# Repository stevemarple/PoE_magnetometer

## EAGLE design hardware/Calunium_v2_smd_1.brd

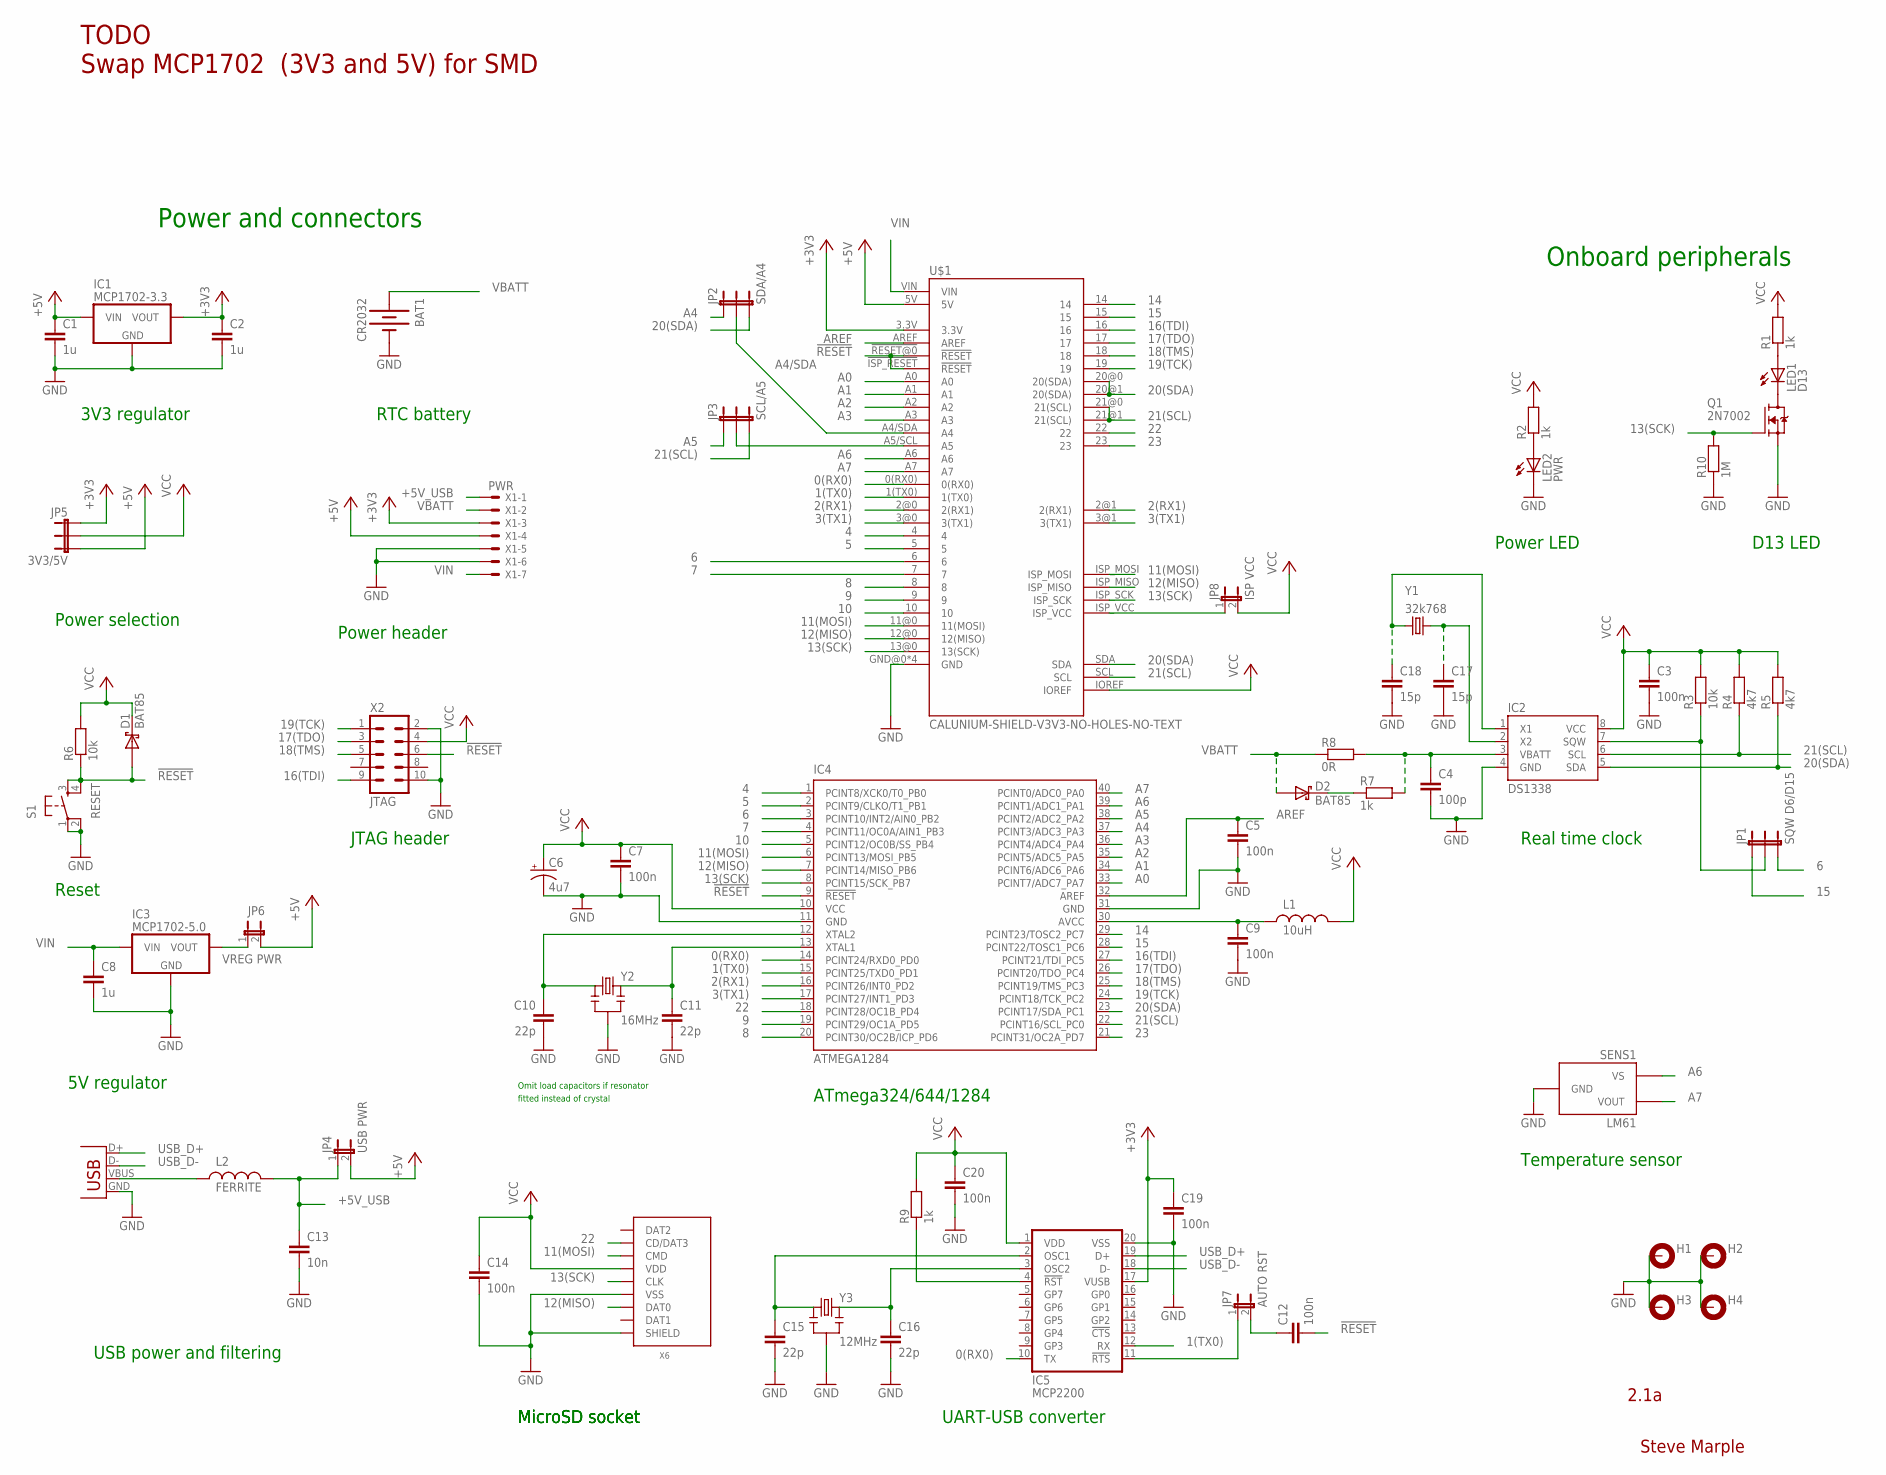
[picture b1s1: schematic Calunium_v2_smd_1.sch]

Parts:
BAT1: CR2032; BATTCOM_20MM_PTH
C1, C2, C8: 1u; 1206-HAND
C3, C5, C7, C9, C12, C14, C19, C20: 100n; 1206-HAND
C4: 100p; 1206-HAND
C6: 4u7; CPOL-RADIAL-10UF-25V
C10, C11, C15, C16: 22p; 0805-HAND
C13: 10n; 1206-HAND
C17, C18: 15p; 0805-HAND
D1, D2: BAT85; SOT23-3-HAND
H1, H2, H3, H4: MOUNT-PAD-ROUND3.0; 3,0-PAD
IC1: MCP1702-3.3; TO-92
IC2: DS1338; SO08
IC3: MCP1702-5.0; TO-92
IC4: ATMEGA1284; DIL40
IC5: MCP2200; SO20
JP1: SQW D6/D15; 1X03
JP2: SDA/A4; 1X03
JP3: SCL/A5; 1X03
JP4: USB PWR; 1X02
JP5: 3V3/5V; 1X03
JP6: VREG PWR; 1X02
JP7: AUTO RST; 1X02
JP8: ISP VCC; 1X02
L1: 10uH; 1210-HAND
L2: FERRITE; 0805-HAND
LED1: D13; LED3MM
LED2: PWR; LED3MM
Q1: 2N7002; SOT23-3-ROTATED
R1, R2, R7, R9: 1k; 1206-HAND
R3, R6: 10k; 1206-HAND
R4, R5: 4k7; 1206-HAND
R8: 0R; 1206-HAND
R10: 1M; 1206-HAND
S1: RESET; TACTILE-PTH
SENS1: LM61; TO-92
U$1: CALUNIUM-SHIELD-V3V3-NO-HOLES-NO-TEXT; CALUNIUM-SHIELD-NO-OUTLINE-NO-HOLES-NO-TEXT-V3
X1: PWR; 22-23-2071
X2: JTAG; CON-HARTING-ML10
X3: USB; USB-B-PTH
X6: MICRO-SD-SOCKETHIROSE-DM3D; MICRO-SD-SOCKET-HIROSE-DM3D
Y1: 32k768; TC38H
Y2: 16MHz; HC49U-V-RESONATOR
Y3: 12MHz; HC49U-V-RESONATOR

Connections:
0(RX0): IC4.14 (PCINT24/RXD0_PD0), IC5.10 (TX), U$1.0(RX0)
1(TX0): IC4.15 (PCINT25/TXD0_PD1), IC5.12 (RX), U$1.1(TX0)
2(RX1): IC4.16 (PCINT26/INT0_PD2), U$1.2@0 (2(RX1)), U$1.2@1 (2(RX1))
3(TX1): IC4.17 (PCINT27/INT1_PD3), U$1.3@0 (3(TX1)), U$1.3@1 (3(TX1))
4: IC4.1 (PCINT8/XCK0/T0_PB0), U$1.4
5: IC4.2 (PCINT9/CLKO/T1_PB1), U$1.5
6: IC4.3 (PCINT10/INT2/AIN0_PB2), JP1.3, U$1.6
7: IC4.4 (PCINT11/OC0A/AIN1_PB3), U$1.7
8: IC4.20 (PCINT30/OC2B/ICP_PD6), U$1.8
9: IC4.19 (PCINT29/OC1A_PD5), U$1.9
10: IC4.5 (PCINT12/OC0B/SS_PB4), U$1.10
11(MOSI): IC4.6 (PCINT13/MOSI_PB5), U$1.11@0 (11(MOSI)), U$1.ISP_MOSI, X6.CMD
12(MISO): IC4.7 (PCINT14/MISO_PB6), U$1.12@0 (12(MISO)), U$1.ISP_MISO, X6.DAT0
13(SCK): IC4.8 (PCINT15/SCK_PB7), Q1.1 (G), R10.2, U$1.13@0 (13(SCK)), U$1.ISP_SCK, X6.CLK
14: IC4.29 (PCINT23/TOSC2_PC7), U$1.14
15: IC4.28 (PCINT22/TOSC1_PC6), JP1.1, U$1.15
16(TDI): IC4.27 (PCINT21/TDI_PC5), U$1.16, X2.9 (TDI)
17(TDO): IC4.26 (PCINT20/TDO_PC4), U$1.17, X2.3 (TDO)
18(TMS): IC4.25 (PCINT19/TMS_PC3), U$1.18, X2.5 (TMS)
19(TCK): IC4.24 (PCINT18/TCK_PC2), U$1.19, X2.1 (TCK)
20(SDA): IC2.5 (SDA), IC4.23 (PCINT17/SDA_PC1), JP2.3, R5.1, U$1.20@0 (20(SDA)), U$1.20@1 (20(SDA)), U$1.SDA
21(SCL): IC2.6 (SCL), IC4.22 (PCINT16/SCL_PC0), JP3.3, R4.1, U$1.21@0 (21(SCL)), U$1.21@1 (21(SCL)), U$1.SCL
22: IC4.18 (PCINT28/OC1B_PD4), U$1.22, X6.CD/DAT3
23: IC4.21 (PCINT31/OC2A_PD7), U$1.23
!MCP2200_RESET: IC5.4 (!RST), R9.1
!RESET: C12.2, D1.1 (A), IC4.9 (!RESET), R6.1, S1.3, S1.4, U$1.!ISP_RESET (!RESET), U$1.!RESET@0 (!RESET), X2.6 (!SRST)
+3V3: C2.1, C19.1, IC1.3 (VOUT), IC5.17 (VUSB), JP5.1, U$1.3.3V, X1.3
+5V: C1.1, IC1.2 (VIN), JP4.2, JP5.3, JP6.2, U$1.5V, X1.4
+5V_USB: C13.1, JP4.1, L2.2, X1.1
A0: IC4.33 (PCINT7/ADC7_PA7), U$1.A0
A1: IC4.34 (PCINT6/ADC6_PA6), U$1.A1
A2: IC4.35 (PCINT5/ADC5_PA5), U$1.A2
A3: IC4.36 (PCINT4/ADC4_PA4), U$1.A3
A4: IC4.37 (PCINT3/ADC3_PA3), JP2.1
A4/SDA: JP2.2, U$1.A4/SDA (A4)
A5: IC4.38 (PCINT2/ADC2_PA2), JP3.1
A5/SCL: JP3.2, U$1.A5/SCL (A5)
A6: IC4.39 (PCINT1/ADC1_PA1), SENS1.1 (VS), U$1.A6
A7: IC4.40 (PCINT0/ADC0_PA0), SENS1.2 (VOUT), U$1.A7
AREF: C5.1, IC4.32 (AREF), U$1.AREF
AUTO_RESET: IC5.11 (!RTS), JP7.1
AVCC: C9.1, IC4.30 (AVCC), L1.1
GND: BAT1.2 (-), C1.2, C2.2, C3.2, C4.2, C5.2, C6.2 (-), C7.2, C8.2, C9.2, C10.2, C11.2, C13.2, C14.2, C15.2, C16.2, C17.2, C18.2, C19.2, C20.2, H1.B3,0, H2.B3,0, H3.B3,0, H4.B3,0, IC1.1 (GND), IC2.4 (GND), IC3.1 (GND), IC4.11 (GND), IC4.31 (GND), IC5.20 (VSS), LED2.K (C), Q1.2 (S), R10.1, S1.1, S1.2, SENS1.3 (GND), U$1.GND@0 (GND), U$1.GND@1 (GND), U$1.GND@2 (GND), U$1.GND@3 (GND), X1.5, X1.6, X2.2 (GND), X2.10 (GND), X3.GND, X6.GND (VSS), X6.SHIELD@0 (SHIELD), Y2.GND (2), Y3.GND (2)
unnamed: C11.1, IC4.13 (XTAL1), Y2.2 (3)
unnamed: C10.1, IC4.12 (XTAL2), Y2.1
unnamed: LED1.A, R1.1
unnamed: LED1.K (C), Q1.3 (D)
unnamed: C18.1, IC2.1 (X1), Y1.2
unnamed: JP8.1, U$1.ISP_VCC
unnamed: C16.1, IC5.3 (OSC2), Y3.2 (3)
unnamed: LED2.A, R2.1
unnamed: D2.3 (C), R7.1
unnamed: C4.1, IC2.3 (VBATT), R7.2, R8.2
unnamed: C17.1, IC2.2 (X2), Y1.1
unnamed: IC3.3 (VOUT), JP6.1
unnamed: C12.1, JP7.2
unnamed: L2.1, X3.VBUS
unnamed: C15.1, IC5.2 (OSC1), Y3.1
SQW: IC2.7 (SQW), JP1.2, R3.1
USB_D+: IC5.19 (D+), X3.D+
USB_D-: IC5.18 (D-), X3.D-
VBATT: BAT1.1 (+), D2.1 (A), R8.1, X1.2
VCC: C3.1, C6.1 (+), C7.1, C14.1, C20.1, D1.3 (C), IC2.8 (VCC), IC4.10 (VCC), IC5.1 (VDD), JP5.2, JP8.2, L1.2, R1.2, R2.2, R3.2, R4.2, R5.2, R6.2, R9.2, U$1.IOREF, X2.4 (VTREF), X6.VDD
VIN: C8.1, IC3.2 (VIN), U$1.VIN, X1.7

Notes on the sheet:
Power and connectors
Onboard peripherals
Real time clock
Temperature sensor
ATmega324/644/1284
USB power and filtering
JTAG header
D13 LED
Reset
Power selection
Power header
3V3 regulator
RTC battery
Power LED
Steve Marple
2.1a
5V regulator
Omit load capacitors if resonator
fitted instead of crystal
MicroSD socket
UART-USB converter
TODO Swap MCP1702 (3V3 and 5V) for SMD

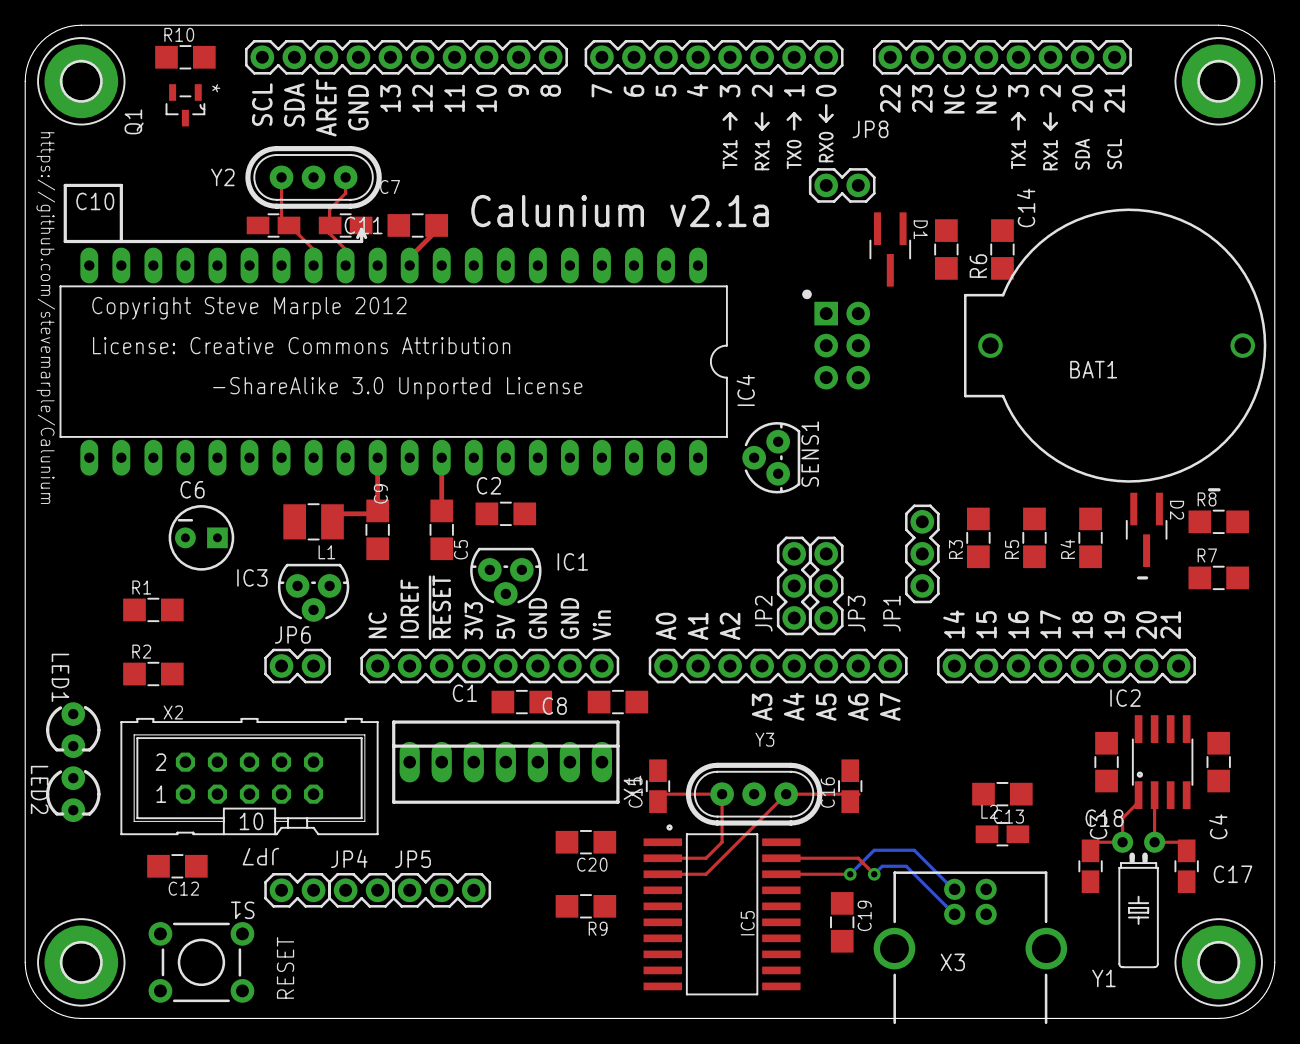
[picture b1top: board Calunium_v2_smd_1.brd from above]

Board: 2 copper layers, 99.1 x 78.7 mm, 65 parts (1 on the bottom side), 64 nets.

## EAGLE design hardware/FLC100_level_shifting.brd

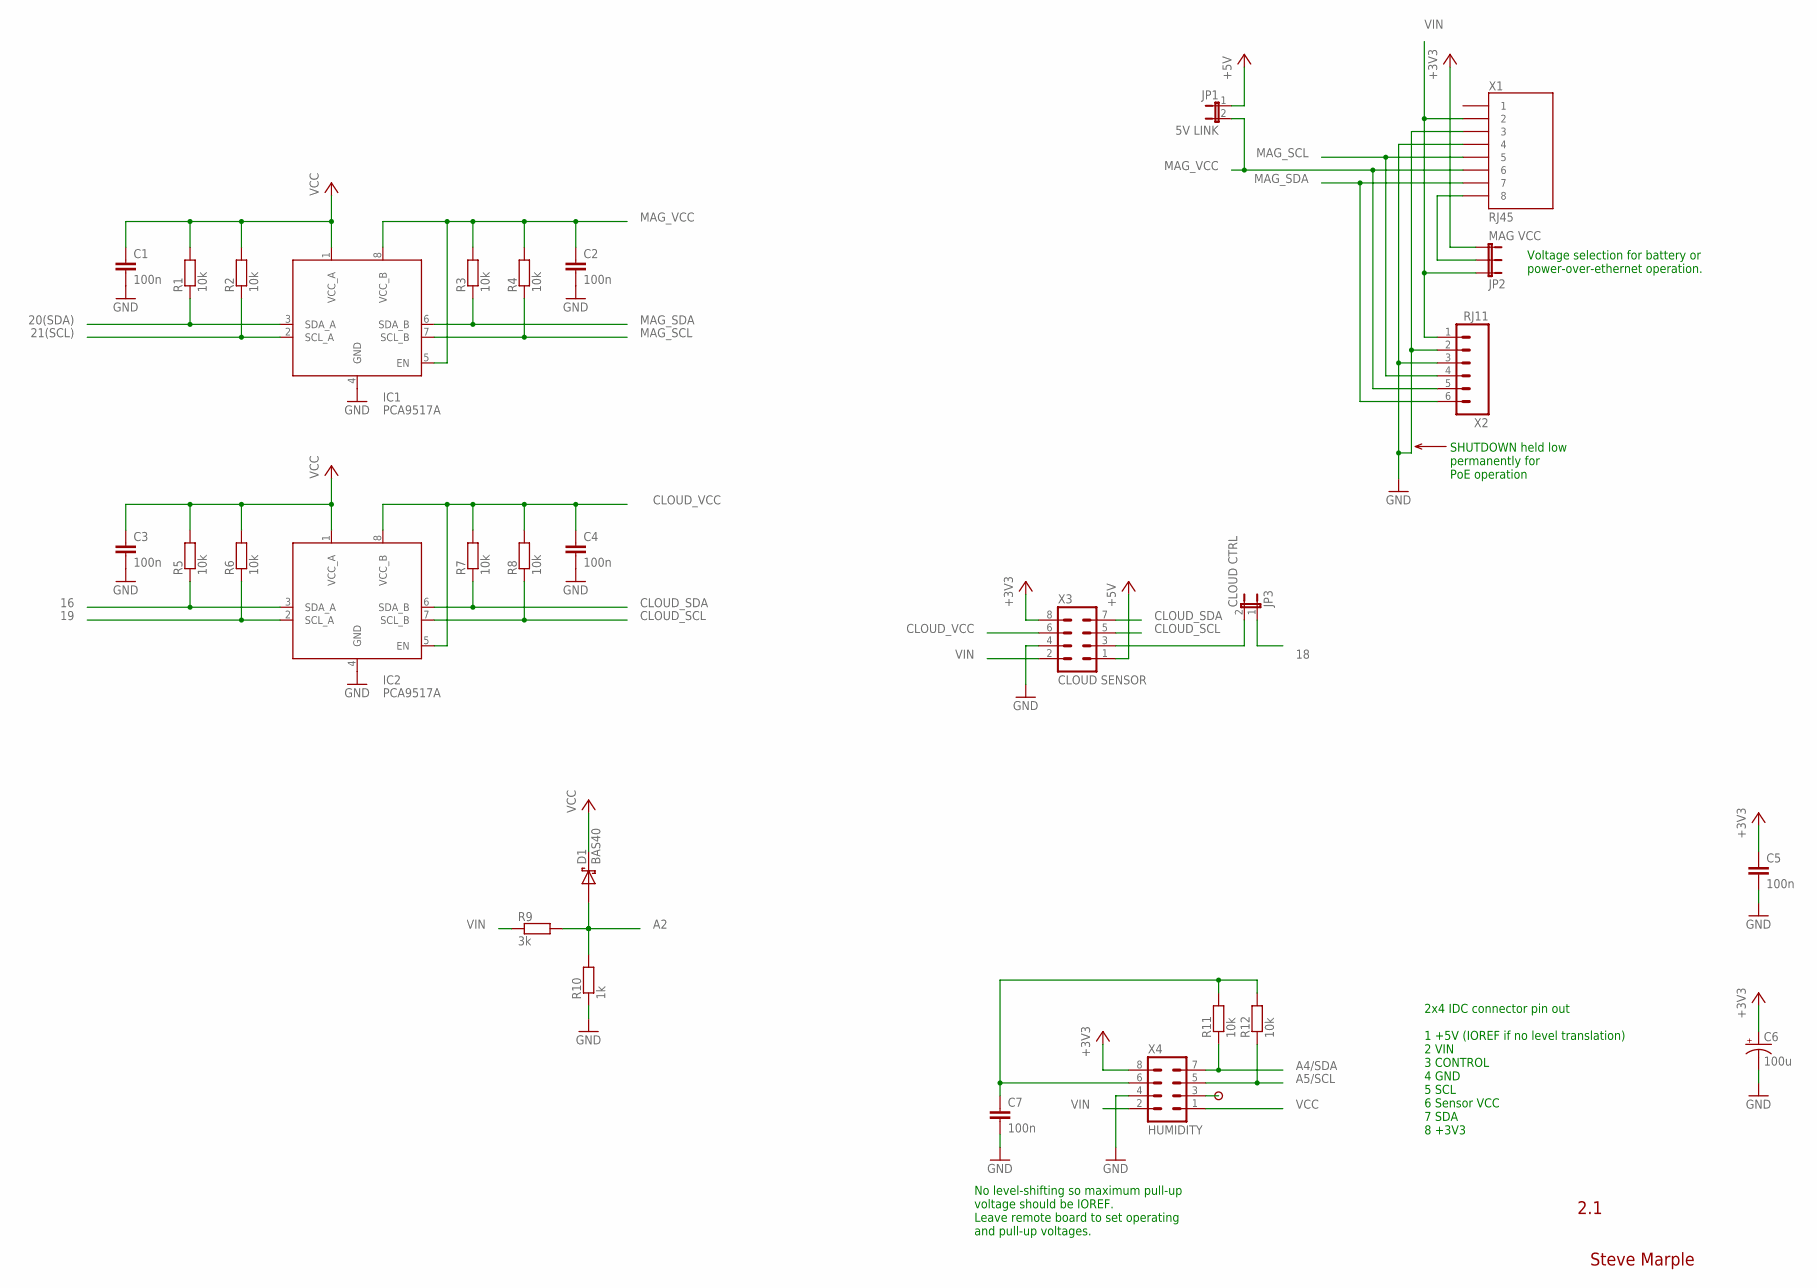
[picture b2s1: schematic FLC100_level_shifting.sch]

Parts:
C1, C2, C3, C4, C5, C7: 100n; 1206-HAND
C6: 100u; CPOL-RADIAL-10UF-25V
D1: BAS40; SOT23-3-HAND
IC1, IC2: PCA9517A; SO08
JP1: 5V LINK; 1X02
JP2: MAG VCC; 1X03
JP3: CLOUD CTRL; 1X02
R1, R2, R3, R4, R5, R6, R7, R8, R11, R12: 10k; 1206-HAND
R9: 3k; 1206-HAND
R10: 1k; 1206-HAND
U$5: PAD
X1: RJ45; RJ45-8
X2: RJ11; RJ11-6
X3: CLOUD SENSOR; ML8
X4: HUMIDITY; ML8

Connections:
16: IC2.3 (SDA_A), R5.1
18: JP3.1
19: IC2.2 (SCL_A), R6.1
20(SDA): IC1.3 (SDA_A), R1.1
21(SCL): IC1.2 (SCL_A), R2.1
+3V3: C5.1, C6.1 (+), JP2.3, X3.8, X4.8
+5V: JP1.1, X3.1
A2: D1.1 (A), R9.2, R10.2
A4/SDA: R11.1, X4.7
A5/SCL: R12.1, X4.5
CLOUD_SCL: IC2.7 (SCL_B), R8.1, X3.5
CLOUD_SDA: IC2.6 (SDA_B), R7.1, X3.7
CLOUD_VCC: C4.1, IC2.5 (EN), IC2.8 (VCC_B), R7.2, R8.2, X3.6
GND: C1.2, C2.2, C3.2, C4.2, C5.2, C6.2 (-), C7.2, IC1.4 (GND), IC2.4 (GND), R10.1, X1.3, X1.4, X2.2, X2.3, X3.4, X4.4
MAG_SCL: IC1.7 (SCL_B), R4.1, X1.5, X2.4
MAG_SDA: IC1.6 (SDA_B), R3.1, X1.7, X2.6
MAG_VCC: C2.1, IC1.5 (EN), IC1.8 (VCC_B), JP1.2, R3.2, R4.2, X1.6, X2.5
unnamed: JP3.2, X3.3
unnamed: JP2.2, X1.8
unnamed: U$5.1, X4.3
unnamed: C7.1, R11.2, R12.2, X4.6
VCC: C1.1, C3.1, D1.3 (C), IC1.1 (VCC_A), IC2.1 (VCC_A), R1.2, R2.2, R5.2, R6.2, X4.1
VIN: JP2.1, R9.1, X1.2, X2.1, X3.2, X4.2

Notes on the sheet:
2.1
Steve Marple
Voltage selection for battery or power-over-ethernet operation.
No level-shifting so maximum pull-up voltage should be IOREF. Leave remote board to set operating and pull-up voltages.
2x4 IDC connector pin out 1 +5V (IOREF if no level translation) 2 VIN 3 CONTROL 4 GND 5 SCL 6 Sensor VCC 7 SDA 8 +3V3
SHUTDOWN held low permanently for PoE operation

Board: 2 copper layers, 30 parts (0 on the bottom side), 22 nets, no tracks yet.

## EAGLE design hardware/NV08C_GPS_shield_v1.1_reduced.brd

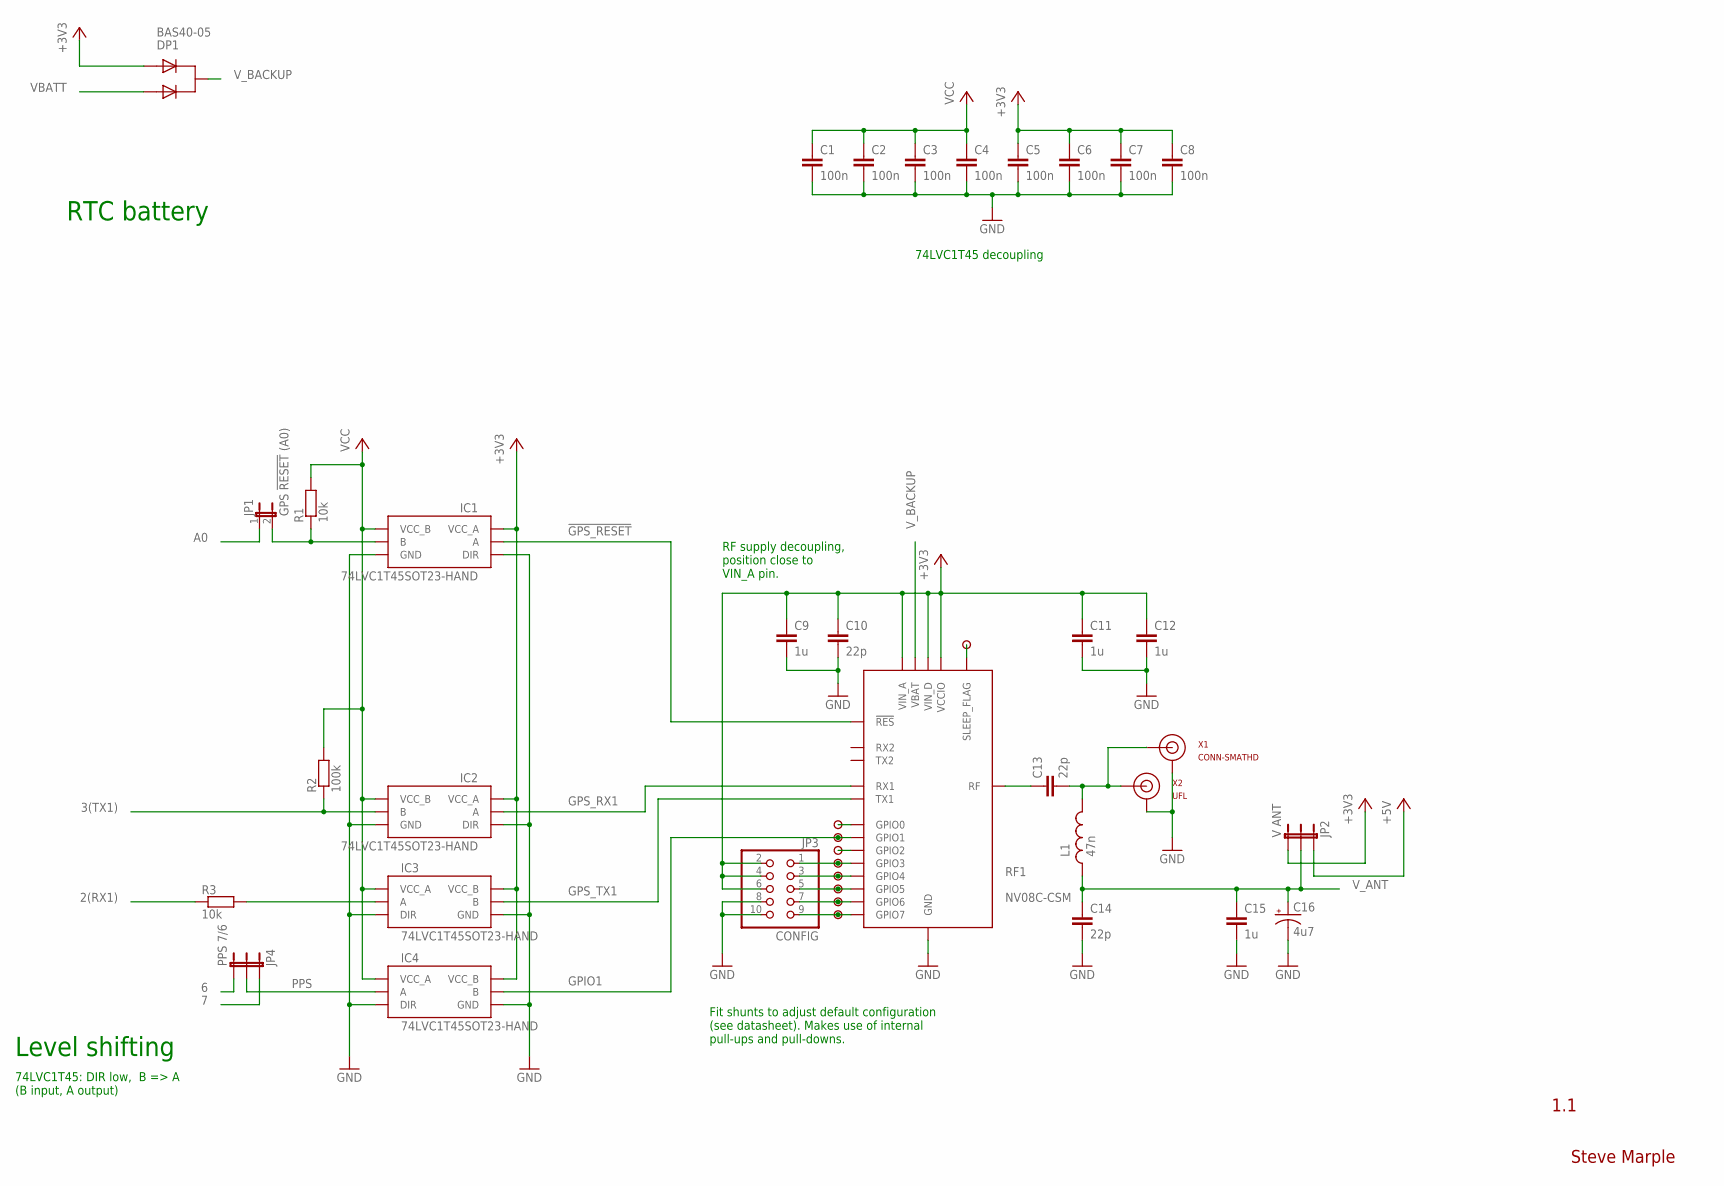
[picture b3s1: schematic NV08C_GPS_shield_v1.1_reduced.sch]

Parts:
C1, C2, C3, C4, C5, C6, C7, C8: 100n; 1206-HAND
C9, C11, C12, C15: 1u; 1206-HAND
C10, C13, C14: 22p; 0805-HAND
C16: 4u7; CPOL-RADIAL-10UF-25V
DP1: BAS40-05; SOT23-3-HAND
IC1, IC2, IC3, IC4: 74LVC1T45SOT23-HAND; SOT23-6-HAND
JP1: GPS !RESET! (A0); 1X02
JP2: V ANT; 1X03
JP3: CONFIG; 2X05
JP4: PPS 7/6; 1X03
L1: 47n; 0805-HAND
R1, R3: 10k; 1206-HAND
R2: 100k; 1206-HAND
RF1: NV08C-CSM; NVC08C-CSM-HAND
U$1, U$2, U$3, U$5, U$6, U$7, U$8, U$9: PAD
U$4: ?; PAD
X1: CONN-SMATHD; SMA-THD
X2: UFL; CONN-UFL-HAND-SOLDERING

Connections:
2(RX1): R3.1
3(TX1): IC2.4 (B), R2.1
6: JP4.3
7: JP4.1
!GPS_RESET: IC1.3 (A), RF1.P$25 (!RES)
+3V3: C5.1, C6.1, C7.1, C8.1, C9.1, C10.1, C11.1, C12.1, DP1.2 (A2), IC1.1 (VCC_A), IC2.1 (VCC_A), IC3.6 (VCC_B), IC4.6 (VCC_B), JP2.3, JP3.2, JP3.4, JP3.6, RF1.P$8 (VIN_A), RF1.P$26 (VIN_D), RF1.P$28 (VCCIO)
+5V: JP2.1
A0: JP1.1
GND: C1.2, C2.2, C3.2, C4.2, C5.2, C6.2, C7.2, C8.2, C9.2, C10.2, C11.2, C12.2, C14.2, C15.2, C16.2 (-), IC1.2 (GND), IC1.5 (DIR), IC2.2 (GND), IC2.5 (DIR), IC3.2 (GND), IC3.5 (DIR), IC4.2 (GND), IC4.5 (DIR), JP3.8, JP3.10, RF1.P$3 (GND), RF1.P$9 (GND), RF1.P$10 (GND), RF1.P$11 (GND), RF1.P$12 (GND), RF1.P$13 (GND), RF1.P$14 (GND), RF1.P$16 (GND), RF1.P$17 (GND), RF1.P$18 (GND), RF1.P$19 (GND), RF1.P$22 (GND), RF1.P$24 (GND), RF1.P$27 (GND), RF1.P$29 (GND), RF1.P$34 (GND), X1.GND@0 (GND), X1.GND@1 (GND), X1.GND@2 (GND), X1.GND@3 (GND), X2.GND@0 (GND), X2.GND@1 (GND)
GPIO0: RF1.P$20 (GPIO0), U$2.1
GPIO1: IC4.4 (B), RF1.P$2 (GPIO1), U$3.1
GPIO2: RF1.P$1 (GPIO2), U$4.1
GPIO3: JP3.1, RF1.P$6 (GPIO3), U$5.1
GPIO4: JP3.3, RF1.P$7 (GPIO4), U$6.1
GPIO5: JP3.5, RF1.P$4 (GPIO5), U$7.1
GPIO6: JP3.7, RF1.P$35 (GPIO6), U$8.1
GPIO7: JP3.9, RF1.P$5 (GPIO7), U$9.1
GPS_RX1: IC2.3 (A), RF1.P$33 (RX1)
GPS_TX1: IC3.4 (B), RF1.P$32 (TX1)
unnamed: C13.2, L1.2, X1.SIG (SIGNAL), X2.SIGNAL
unnamed: IC3.3 (A), R3.2
unnamed: C13.1, RF1.P$15 (RF)
unnamed: IC1.4 (B), JP1.2, R1.1
PPS: IC4.3 (A), JP4.2
SLEEP_FLAG: RF1.P$21 (SLEEP_FLAG), U$1.1
VBATT: DP1.1 (A1)
VCC: C1.1, C2.1, C3.1, C4.1, IC1.6 (VCC_B), IC2.6 (VCC_B), IC3.1 (VCC_A), IC4.1 (VCC_A), R1.2, R2.2
V_ANT: C14.1, C15.1, C16.1 (+), JP2.2, L1.1
V_BACKUP: DP1.3 (C), RF1.P$23 (VBAT)

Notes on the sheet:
1.1
Steve Marple
Level shifting
RTC battery
74LVC1T45: DIR low, B => A (B input, A output)
RF supply decoupling, position close to VIN_A pin.
Fit shunts to adjust default configuration (see datasheet). Makes use of internal pull-ups and pull-downs.
74LVC1T45 decoupling

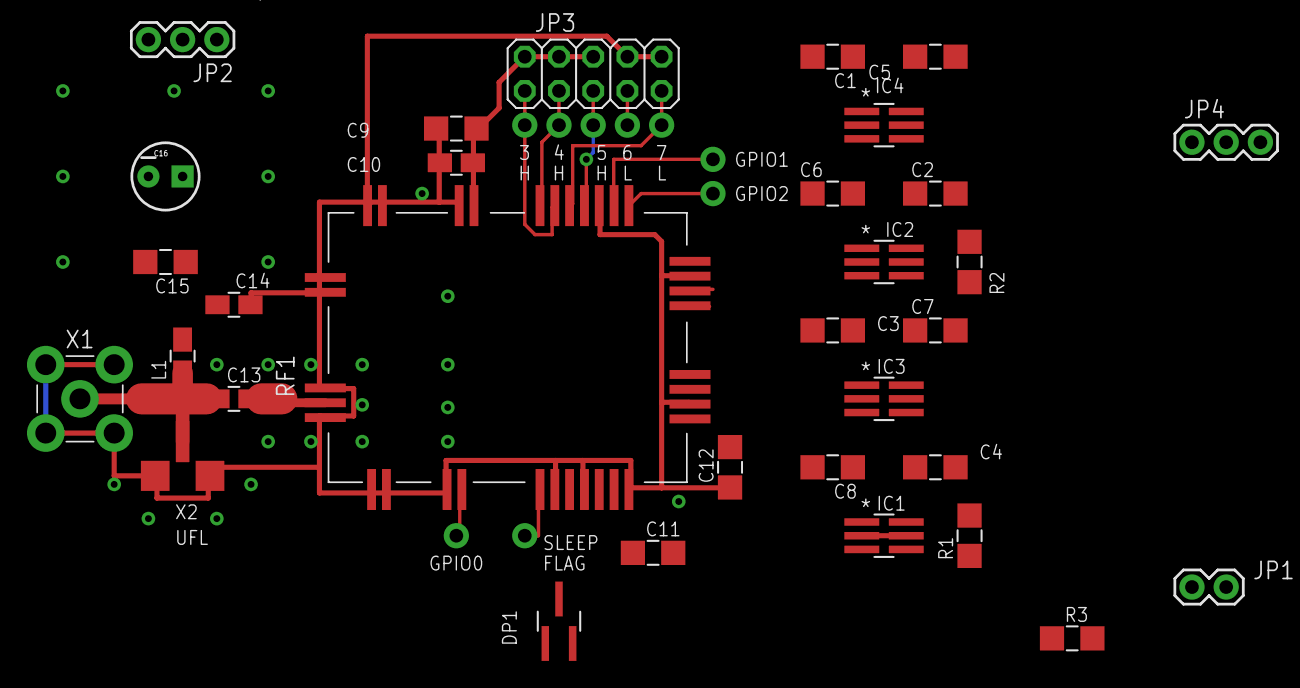
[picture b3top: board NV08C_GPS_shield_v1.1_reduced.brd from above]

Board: 2 copper layers, 41 parts (0 on the bottom side), 23 nets.

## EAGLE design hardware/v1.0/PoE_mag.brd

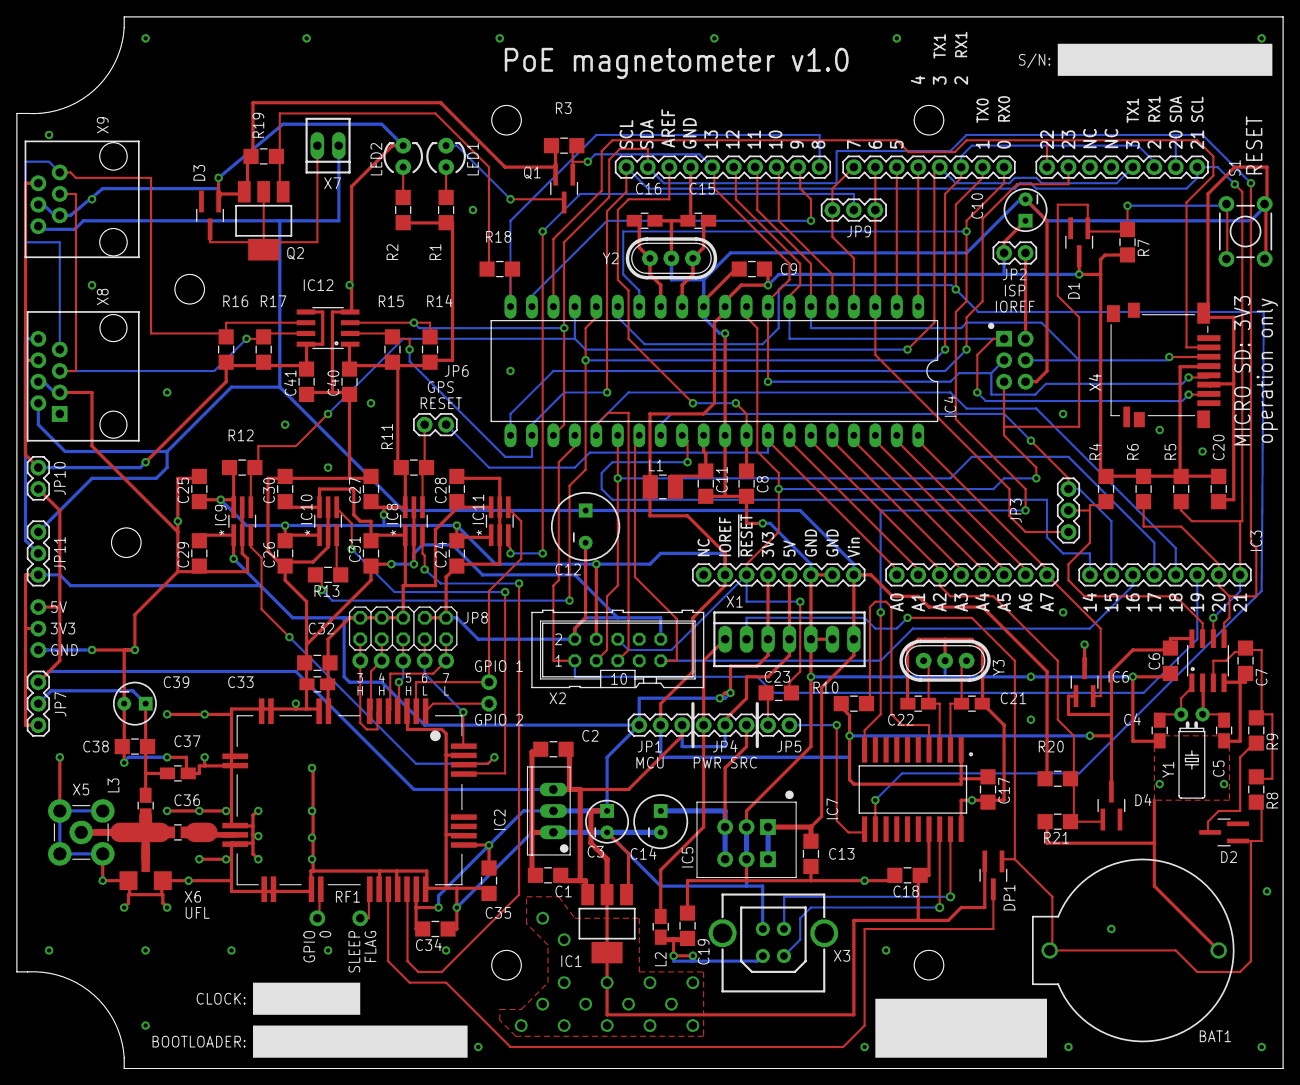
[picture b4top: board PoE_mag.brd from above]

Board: 2 copper layers, 149.9 x 124.5 mm, 126 parts (0 on the bottom side), 87 nets.

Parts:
BAT1: CR2032; BATTCOM_20MM_PTH
BOX1: BOXPOE-MAG-150-150; FIBOX-PC-M-95-G-POE-MAG
C1, C2, C13, C32, C34, C35, C38: 1u; 1206-HAND
C3, C10, C39: 10u; CPOL-RADIAL-10UF-25V
C4, C5: 15p; 0805-HAND
C6, C8, C9, C11, C17, C18, C20, C23, C24, C25, C26, C27, C28, C29, C30, C31, C40, C41: 100n; 1206-HAND
C7: 100p; 1206-HAND
C12: 100u 25V; CPOL-RADIAL-100UF-25V-150MIL
C14: 100u; CPOL-RADIAL-100UF-16V
C15, C16, C21, C22, C33, C36, C37: 22p; 0805-HAND
C19: 10n; 1206-HAND
D1, D2, D4: BAS40; SOT23-3-HAND
D3: BAS21; SOT23-3-HAND
DP1: BAS40-05; SOT23-3-HAND
IC1: LD1117V33; SOT223-HAND
IC2: LD1117V33; TO220
IC3: DS1338; SO08
IC4: ATMEGA1284; DIL40
IC5: TSR 1-2450; TSR-1-XXXX/POWERPAX-P78XX-10
IC6: LM61; SOT23-3-HAND
IC7: MCP2200; SO20
IC8, IC9, IC10, IC11: 74LVC1T45SOT23-HAND; SOT23-6-HAND
IC12: PCA9517A; SO08
JP1: 3V3/5V; 1X03
JP2: ISP IOREF; 1X02
JP3: SQW; 1X03
JP4: USB/VIN; 1X03
JP5: AUTO RST; 1X02
JP6: GPS !RESET! (A0); 1X02
JP7: V ANT; 1X03
JP8: CONFIG; 2X05
JP9: PPS; 1X03
JP10: 5V LINK; 1X02
JP11: MAG VCC; 1X03
L1: 10uH; 1210-HAND
L2: FERRITE; 0805-HAND
L3: 47n; 0805-HAND
LED1: D13; LED3MM
LED2: PWR; LED3MM
Q1: BSS138; SOT23-3-HAND
Q2: BUK98150-55A; SOT223-HAND
R1, R2: 560R; 1206-HAND
R3, R19: 1M; 1206-HAND
R4, R7, R11, R13: 10k; 1206-HAND
R5, R6, R14, R15, R16, R17: 4k7; 1206-HAND
R8: 0R; 1206-HAND
R9, R10: 1k; 1206-HAND
R12: 100k; 1206-HAND
R18: 330R; 1206-HAND
R20: 3k 1%; 1206-HAND
R21: 1k 1%; 1206-HAND
RF1: NV08C-CSM; NVC08C-CSM-HAND
S1: RESET; TACTILE-PTH
U$1: CALUNIUM-SHIELD-V3V3-NO-HOLES-NO-TEXT; CALUNIUM-SHIELD-NO-OUTLINE-NO-HOLES-NO-TEXT-V3
U$2, U$3, U$4, U$5, U$6, U$7, U$9, U$10, U$11, U$12, U$13: PAD
U$8: ?; PAD
X1: PWR; 22-23-2071
X2: JTAG; CON-HARTING-ML10
X3: USB; USB-B-PTH-VERTICAL
X4: MICRO-SD-SOCKETHIROSE-DM3D; MICRO-SD-SOCKET-HIROSE-DM3D
X5: CONN-SMATHD; SMA-THD
X6: UFL; CONN-UFL-HAND-SOLDERING
X7: 22-23-2021
X8: RJ45; RJ45-8
X9: RJ11; RJ11-6
Y1: 32k768; TC38H
Y2: 16MHz; HC49U-V-RESONATOR
Y3: 12MHz; HC49U-V-RESONATOR

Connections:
0(RX0): IC4.14, IC7.10, U$1.0(RX0)
1(TX0): IC4.15, IC7.12, U$1.1(TX0)
2(RX1): IC4.16, R13.1, U$1.2@0, U$1.2@1
3(TX1): IC4.17, IC9.4, R12.1, U$1.3@0, U$1.3@1
4: IC4.1, U$1.4
5: IC4.2, U$1.5
6: IC4.3, JP3.3, JP9.3, U$1.6
7: IC4.4, JP9.1, U$1.7
8: IC4.20, R18.1, U$1.8
9: IC4.19, U$1.9
10: IC4.5, U$1.10
11(MOSI): IC4.6, U$1.11@0, U$1.ISP_MOSI, X4.CMD
12(MISO): IC4.7, U$1.12@0, U$1.ISP_MISO, X4.DAT0
13(SCK): IC4.8, Q1.1, R3.2, U$1.13@0, U$1.ISP_SCK, X4.CLK
14: IC4.29, U$1.14
15: IC4.28, JP3.1, U$1.15
16(TDI): IC4.27, U$1.16, X2.9
17(TDO): IC4.26, U$1.17, X2.3
18(TMS): IC4.25, U$1.18, X2.5
19(TCK): IC4.24, U$1.19, X2.1
20(SDA): IC3.5, IC4.23, IC12.3, R6.1, R14.1, U$1.20@0, U$1.20@1, U$1.SDA
21(SCL): IC3.6, IC4.22, IC12.2, R5.1, R15.1, U$1.21@0, U$1.21@1, U$1.SCL
22: IC4.18, U$1.22, X4.CD/DAT3
23: IC4.21, U$1.23
!GPS_RESET: IC8.3, RF1.P$25
!MCP2200_RESET: IC7.4, R10.1
!RESET: C23.2, D1.1, IC4.9, R7.1, S1.3, S1.4, U$1.!ISP_RESET, U$1.!RESET@0, X2.6
+3V3: C3.1, C18.1, C28.1, C29.1, C30.1, C31.1, C32.1, C33.1, C34.1, C35.1, DP1.2, IC1.2, IC1.4, IC2.2, IC7.17, IC8.1, IC9.1, IC10.6, IC11.6, JP1.1, JP7.3, JP8.2, JP8.4, JP8.6, JP11.3, RF1.P$8, RF1.P$26, RF1.P$28, U$1.3.3V, U$3.1, X1.3
+5V: C1.1, C2.1, IC1.3, IC2.3, JP1.3, JP4.2, JP7.1, JP10.1, U$1.5V, U$4.1, X1.4
+5V_USB: JP4.3, L2.2, X1.1
A0: IC4.33, JP6.1, U$1.A0
A1: IC4.34, U$1.A1
A2: D4.1, IC4.35, R20.2, R21.2, U$1.A2
A3: IC4.36, U$1.A3
A4: IC4.37, U$1.A4/SDA
A5: IC4.38, U$1.A5/SCL
A6: IC4.39, U$1.A6
A7: IC4.40, IC6.2, U$1.A7
AREF: C8.1, IC4.32, U$1.AREF
AUTO_RESET: IC7.11, JP5.1
AVCC: C11.1, IC4.30, L1.1
FAN_CTRL: D3.3, Q2.2, Q2.4, X7.2
GND: BAT1.2, C1.2, C2.2, C3.2, C4.2, C5.2, C6.2, C7.2, C8.2, C9.2, C10.2, C11.2, C12.2, C13.2, C14.2, C15.2, C16.2, C17.2, C18.2, C19.2, C20.2, C21.2, C22.2, C24.2, C25.2, C26.2, C27.2, C28.2, C29.2, C30.2, C31.2, C32.2, C33.2, C34.2, C35.2, C37.2, C38.2, C39.2, C40.2, C41.2, D3.1, IC1.1, IC2.1, IC3.4, IC4.11, IC4.31, IC5.2@A, IC5.2@B, IC6.3, IC7.20, IC8.2, IC8.5, IC9.2, IC9.5, IC10.2, IC10.5, IC11.2, IC11.5, IC12.4, JP8.8, JP8.10, LED2.K, Q1.2, Q2.3, R3.1, R19.1, R21.1, RF1.P$3, RF1.P$9, RF1.P$10, RF1.P$11, RF1.P$12, RF1.P$13, RF1.P$14, RF1.P$16, RF1.P$17, RF1.P$18, RF1.P$19, RF1.P$22, RF1.P$24, RF1.P$27, RF1.P$29, RF1.P$34, S1.1, S1.2, U$1.GND@0, U$1.GND@1, U$1.GND@2, U$1.GND@3, U$2.1, X1.5, X1.6, X2.2, X2.10, X3.GND, X4.GND, X4.SHIELD@0, X5.GND@0, X5.GND@1, X5.GND@2, X5.GND@3, X6.GND@0, X6.GND@1, X8.3, X8.4, X9.2, X9.3, Y2.GND, Y3.GND
GPIO0: RF1.P$20, U$6.1
GPIO1: IC11.4, RF1.P$2, U$7.1
GPIO2: RF1.P$1, U$8.1
GPIO3: JP8.1, RF1.P$6, U$9.1
GPIO4: JP8.3, RF1.P$7, U$10.1
GPIO5: JP8.5, RF1.P$4, U$11.1
GPIO6: JP8.7, RF1.P$35, U$12.1
GPIO7: JP8.9, RF1.P$5, U$13.1
GPS_RX1: IC9.3, RF1.P$33
GPS_TX1: IC10.4, RF1.P$32
MAG_SCL: IC12.7, R17.1, X8.5, X9.4
MAG_SDA: IC12.6, R16.1, X8.7, X9.6
MAG_VCC: C41.1, IC12.5, IC12.8, JP10.2, R16.2, R17.2, X8.6, X9.5
unnamed: C16.1, IC4.13, Y2.2
unnamed: C15.1, IC4.12, Y2.1
unnamed: LED1.A, R1.1
unnamed: LED1.K, Q1.3
unnamed: C4.1, IC3.1, Y1.2
unnamed: JP2.1, U$1.ISP_VCC
unnamed: C22.1, IC7.3, Y3.2
unnamed: LED2.A, R2.1
unnamed: D2.3, R9.1
unnamed: C7.1, IC3.3, R8.2, R9.2
unnamed: C5.1, IC3.2, Y1.1
unnamed: C14.1, IC5.3@A, IC5.3@B, JP4.1
unnamed: C23.1, JP5.2
unnamed: C21.1, IC7.2, Y3.1
unnamed: IC8.4, JP6.2, R11.1
unnamed: C36.2, L3.2, X5.SIG, X6.SIGNAL
unnamed: C36.1, RF1.P$15
unnamed: IC10.3, R13.2
unnamed: JP11.2, X8.8
unnamed: Q2.1, R18.2, R19.2
PPS: IC11.3, JP9.2
SLEEP_FLAG: RF1.P$21, U$5.1
SQW: IC3.7, JP3.2, R4.1
USB_D+: IC7.19, X3.D+
USB_D-: IC7.18, X3.D-
VBATT: BAT1.1, D2.1, DP1.1, R8.1, X1.2
VBUS: C19.1, L2.1, X3.VBUS
VCC: C6.1, C9.1, C10.1, C17.1, C20.1, C24.1, C25.1, C26.1, C27.1, C40.1, D1.3, D4.3, IC3.8, IC4.10, IC6.1, IC7.1, IC8.6, IC9.6, IC10.1, IC11.1, IC12.1, JP1.2, JP2.2, L1.2, R1.2, R2.2, R4.2, R5.2, R6.2, R7.2, R10.2, R11.2, R12.2, R14.2, R15.2, U$1.IOREF, X2.4, X4.VDD
VIN: C12.1, C13.1, IC5.1@A, IC5.1@B, JP11.1, R20.1, U$1.VIN, X1.7, X7.1, X8.2, X9.1
V_ANT: C37.1, C38.1, C39.1, JP7.2, L3.1
V_BACKUP: DP1.3, RF1.P$23

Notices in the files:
hardware/Calunium_v2_smd_1.brd:
License: Creative Commons Attribution
Copyright Steve Marple 2012
parts and their libraries:
SparkFun: Licensing: CC v3.0 Share-Alike You are welcome to use this library for commercial purposes.
